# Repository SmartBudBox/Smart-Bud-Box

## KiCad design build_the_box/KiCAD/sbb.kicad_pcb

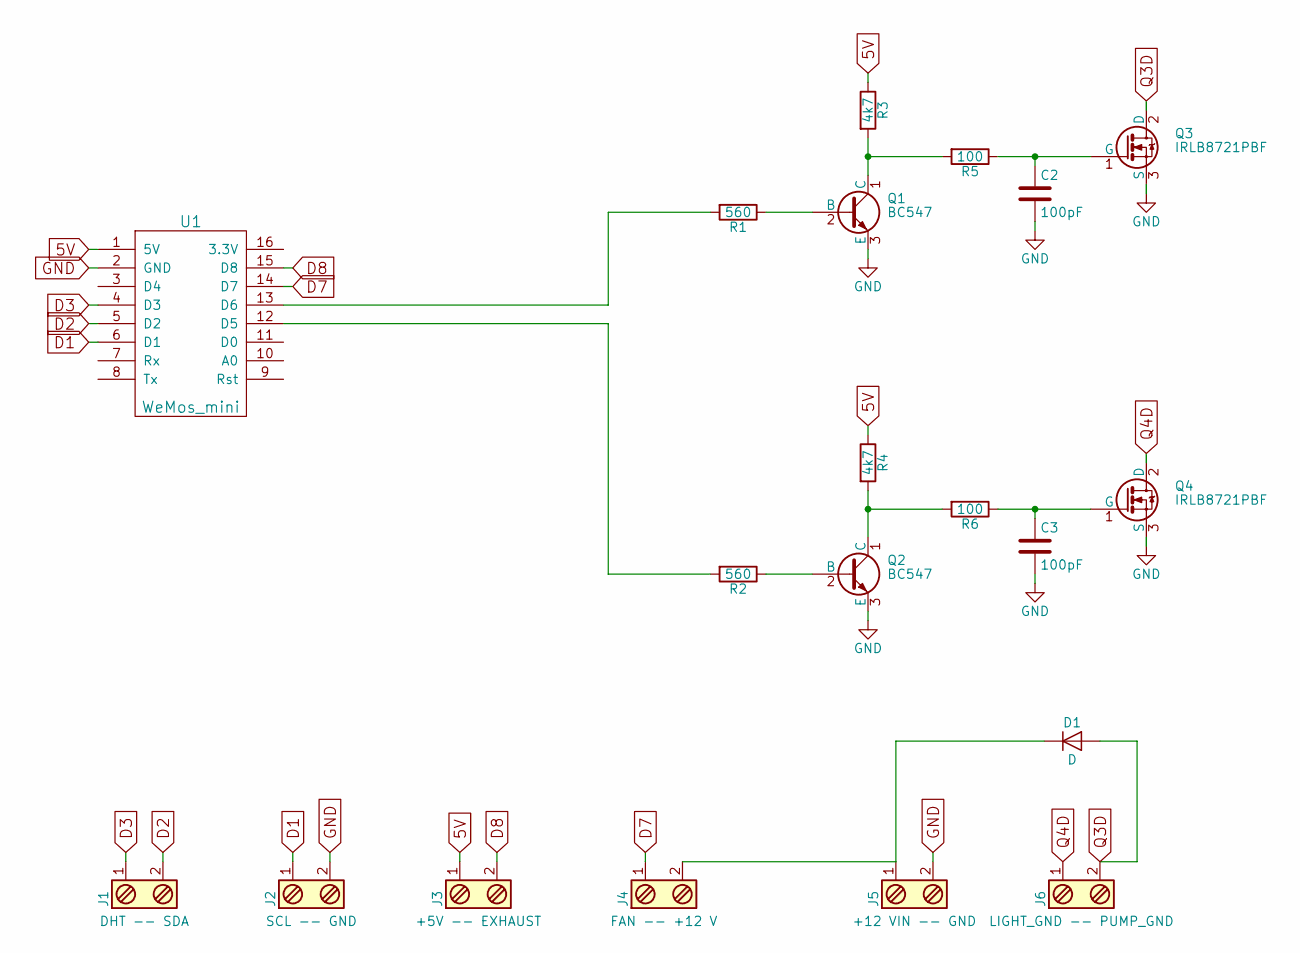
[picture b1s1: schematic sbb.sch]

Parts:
C2, C3: 100pF; C_Disc_D3.0mm_W2.0mm_P2.50mm
D1: D; D_5W_P10.16mm_Horizontal
J1: DHT -- SDA; TerminalBlock_Pheonix_MKDS1.5-2pol
J2: SCL -- GND; TerminalBlock_Pheonix_MKDS1.5-2pol
J3: +5V -- EXHAUST; TerminalBlock_Pheonix_MKDS1.5-2pol
J4: FAN -- +12 V; TerminalBlock_Pheonix_MKDS1.5-2pol
J5: +12 VIN -- GND; TerminalBlock_Pheonix_MKDS1.5-2pol
J6: LIGHT_GND -- PUMP_GND; TerminalBlock_Pheonix_MKDS1.5-2pol
Q1, Q2: BC547; TO-92_Molded_Narrow
Q3, Q4: IRLB8721PBF; TO-220_Vertical
R1, R2: 560; R_Axial_DIN0207_L6.3mm_D2.5mm_P10.16mm_Horizontal
R3, R4: 4k7; R_Axial_DIN0207_L6.3mm_D2.5mm_P10.16mm_Horizontal
R5, R6: 100; R_Axial_DIN0207_L6.3mm_D2.5mm_P10.16mm_Horizontal
U1: WeMos_mini; wemos_d1_mini

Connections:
5V: J3.1, R3.1, R4.1, U1.1 (5V)
D1: J2.1, U1.6 (D1)
D2: J1.2, U1.5 (D2)
D3: J1.1, U1.4 (D3)
D7: J4.1, U1.14 (D7)
D8: J3.2, U1.15 (D8)
GND: C2.2, C3.2, J2.2, J5.2, Q1.3 (E), Q2.3 (E), Q3.3 (S), Q4.3 (S), U1.2 (GND)
unnamed: C2.1, Q3.1 (G), R5.1
unnamed: C3.1, Q4.1 (G), R6.1
unnamed: D1.1 (K), J4.2, J5.1
unnamed: Q1.1 (C), R3.2, R5.2
unnamed: Q1.2 (B), R1.1
unnamed: Q2.1 (C), R4.2, R6.2
unnamed: Q2.2 (B), R2.1
unnamed: R1.2, U1.13 (D6)
unnamed: R2.2, U1.12 (D5)
Q3D: D1.2 (A), J6.2, Q3.2 (D)
Q4D: J6.1, Q4.2 (D)

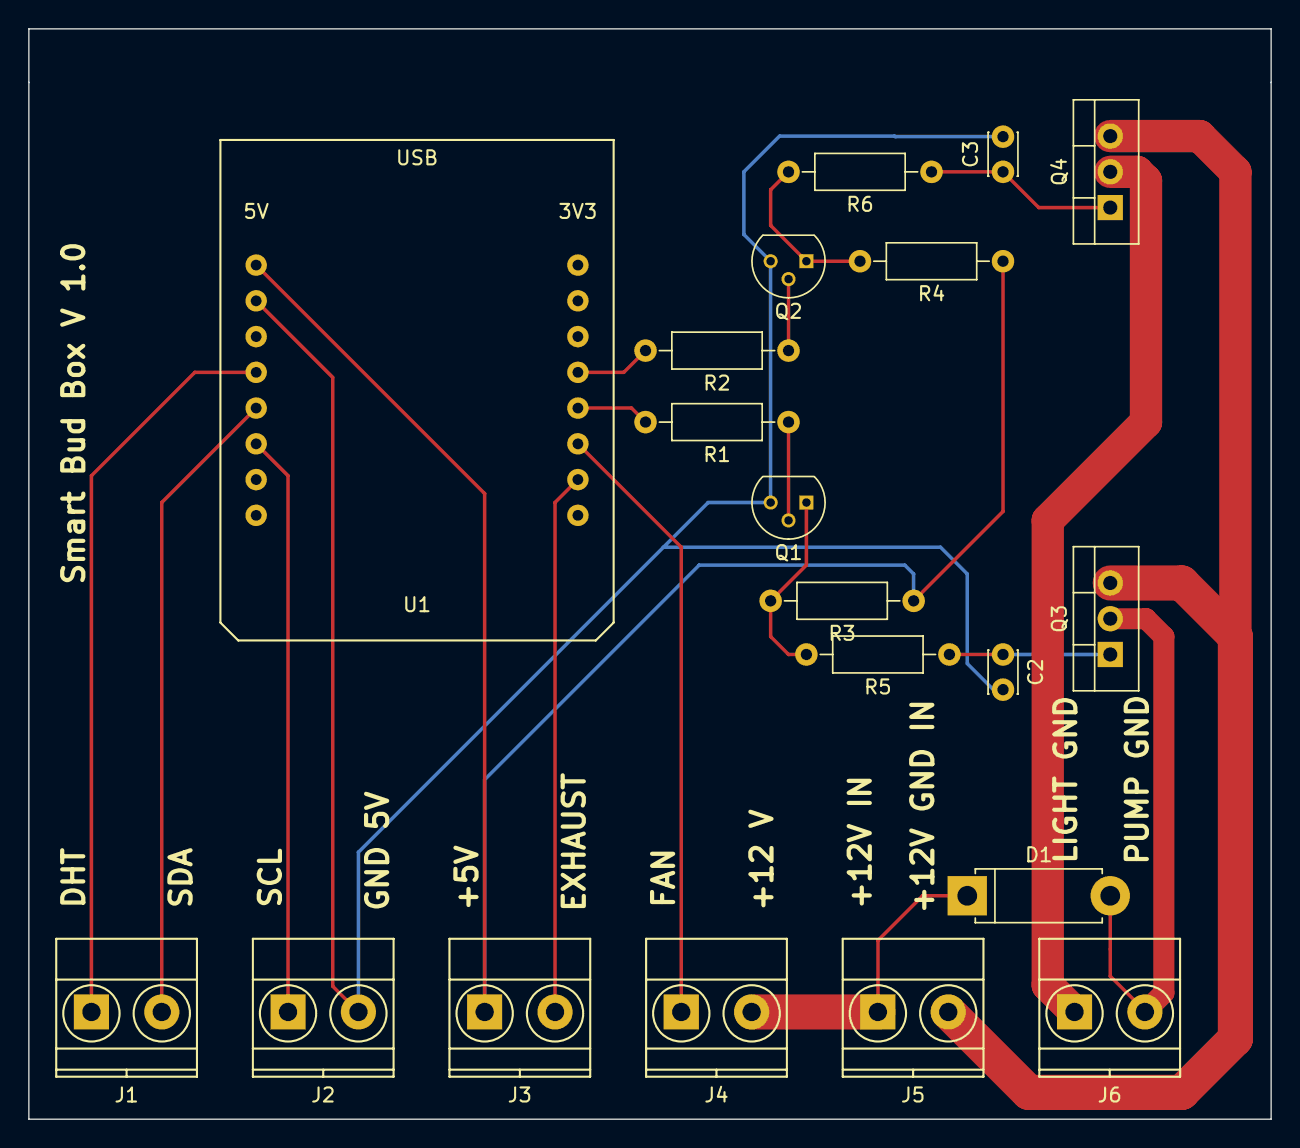
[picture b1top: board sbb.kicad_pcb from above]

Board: 2 copper layers, 88.3 x 77.5 mm, 20 parts (0 on the bottom side), 18 nets.

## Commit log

2017-12-09 Planer works now
    now u can add plans like auto watering or email if an errorr ist there. Also the system recordnize that the water tank is empty and put an error to the box
2018-01-07 bugfix
